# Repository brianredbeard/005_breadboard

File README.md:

# 005 Breadboard Breakout

## About

This is a breakout board for 0.05" (1.27mm) pitch parts so that they may be
connected to a standard 0.1" (2.54mm) pitch breadboard.

It was originally designed for use with the [Olimex iCE40HX8K-EVB][olimex-fpga].
This board uses a series of 40 pin IDC cables with 0.05" pitch which is great
from the perspective of maximizing the footprint of the development board...
it's sub-optimal for any peripheral development.  Additionally, this board
should be usable for other projects with similar footprint needs.

## Files

```
├── 005_breadboard-cache.lib          - a local copy of symbols used in the schematic
├── 005_breadboard.kicad_pcb          - kicad pcb layout file
├── 005_breadboard.pro                - project file (parameters for project)
├── 005_breadboard.sch                - kicad schematic file
├── 005_breadboard_schematic.pdf      - rendering of schematic in PDF
├── 005_breadboard_top.png            - 3d screenshot of board top
├── 005_breadboard_bottom.png         - 3d screenshot of board bottom
├── gerbers                           - gerber files for manufacturing
│   ├── 005_breadboard-B.Cu.gbl
│   ├── 005_breadboard-B.Mask.gbs
│   ├── 005_breadboard-B.SilkS.gbo
│   ├── 005_breadboard.drl
│   ├── 005_breadboard-Edge.Cuts.gm1
│   ├── 005_breadboard-F.Cu.gtl
│   ├── 005_breadboard-F.Mask.gts
│   └── 005_breadboard-F.SilkS.gto
└── .pretty                           - folder of local project footprints
```

## Screenshots

Top of board:

Bottom of board:

## Schematic

A simple PDF of the schematic can be downloaded [here](/005_breadboard_schematic.pdf)

## Bill of Materials

To build this board you will need the following:

| Part # | Quantity | Description |
| --     | --       | --          |
| 2x20 Pin Header | 1 | 2x20 0.05" (1.27mm) Pin header (male or female depending on need) |
| 1x20 Pin header (male) | 2  | 2x20 0.1" (2.54mm) Pin header (male) to be connected to breadboard |

The 0.05" pin headers can be sourced from a number of locations:

  - Olimex  - [female][olimex-ph5-f] / [male][olimex-ph5-m] 
  - Digikey - [female][digikey-ph5-f] / [male][digikey-ph5-m] 

The 0.10" pin headers can be sourced from a number of locations:

  - Digikey - [female][digikey-ph10-f] / [male][digikey-ph10-m] 

## Ordering

The board is currently shared on [OSHPark][oshpark] and can be ordered.  The
cost is $9.95 (USD) with a turnaround time of approximately 15 calendar days.

The Olimex [iCE40HX8K][olimex-fpga-source] evaluation board can be purchased
through [Olimex][olimex-fpga].

## LICENSE

These designs are licensed under the APACHE 2 license [LICENSE](LICENSE).

This design uses the [Olimex][olimex]  2x20 0.05" pitch SMD connectors from
their [KiCAD parts library][olimex-parts], which are also licensed under
APACHE 2.

[olimex]: https://www.olimex.com/
[olimex-fpga]: https://www.olimex.com/Products/FPGA/iCE40/iCE40HX8K-EVB/open-source-hardware
[olimex-fpga-source]: https://github.com/OLIMEX/iCE40HX8K-EVB
[olimex-parts]: https://github.com/OLIMEX/KiCAD
[oshpark]: https://oshpark.com/shared_projects/dG68p194

[olimex-ph5-f]: https://www.olimex.com/Products/Components/Connectors/FEMALE-YAV36P-2x05/
[olimex-ph5-m]: https://www.olimex.com/Products/Components/Connectors/MALE-PAV16X-2x05/

[digikey-ph5-f]: https://www.digikey.com/product-detail/en/amphenol-fci/20021321-00040T4LF/609-3779-ND/2209124
[digikey-ph5-m]: https://www.digikey.com/product-detail/en/harwin-inc/M50-3602042/952-1393-ND/2264374
[digikey-ph10-f]: https://www.digikey.com/product-detail/en/sullins-connector-solutions/PPPC201LFBN-RC/S7053-ND/810192
[digikey-ph10-m]: https://www.digikey.com/product-detail/en/sullins-connector-solutions/PRPC020SAAN-RC/S1011EC-20-ND/2775234

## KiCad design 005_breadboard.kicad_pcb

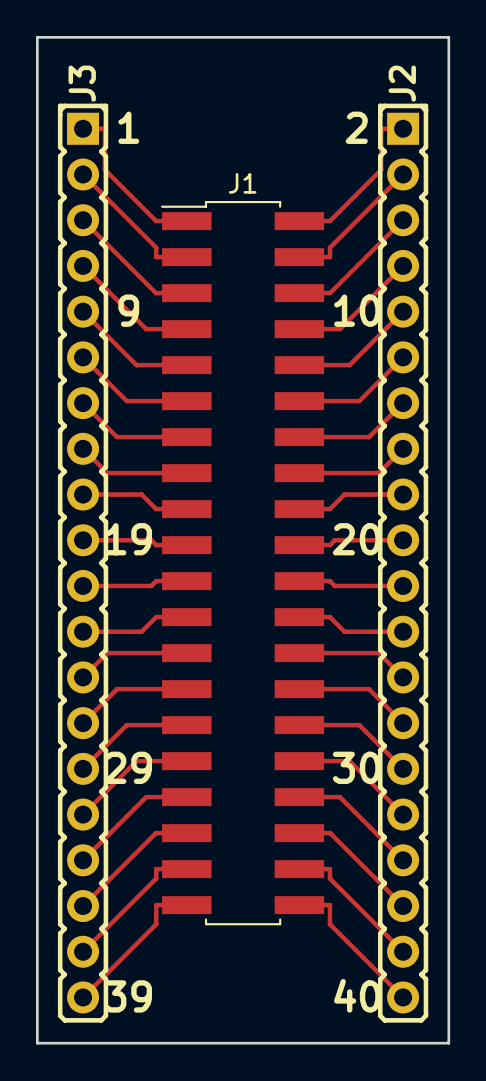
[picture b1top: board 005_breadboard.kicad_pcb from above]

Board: 2 copper layers, 22.9 x 55.9 mm, 3 parts (0 on the bottom side), 40 nets.

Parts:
J1: GPIO 02x20; Pin_Header_Straight_2x20_Pitch2.00mm_SMD
J2, J3: CONN_01X20; HN1x20

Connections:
/A1: J1.1, J3.1
/A2: J1.3, J3.2
/A3: J1.5, J3.3
/A4: J1.7, J3.4
/A5: J1.9, J3.5
/A6: J1.11, J3.6
/A7: J1.13, J3.7
/A8: J1.15, J3.8
/A9: J1.17, J3.9
/A10: J1.19, J3.10
/A11: J1.21, J3.11
/A12: J1.23, J3.12
/A13: J1.25, J3.13
/A14: J1.27, J3.14
/A15: J1.29, J3.15
/A16: J1.31, J3.16
/A17: J1.33, J3.17
/A18: J1.35, J3.18
/A19: J1.37, J3.19
/A20: J1.39, J3.20
/A21: J1.2, J2.1
/A22: J1.4, J2.2
/A23: J1.6, J2.3
/A24: J1.8, J2.4
/A25: J1.10, J2.5
/A26: J1.12, J2.6
/A27: J1.14, J2.7
/A28: J1.16, J2.8
/A29: J1.18, J2.9
/A30: J1.20, J2.10
/A31: J1.22, J2.11
/A32: J1.24, J2.12
/A33: J1.26, J2.13
/A34: J1.28, J2.14
/A35: J1.30, J2.15
/A36: J1.32, J2.16
/A37: J1.34, J2.17
/A38: J1.36, J2.18
/A39: J1.38, J2.19
/A40: J1.40, J2.20

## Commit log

2017-09-20 Open Sourcing the board designs
    The initial order has now been placed with OSHPark so I'll follow up in
    a few weeks with any design tweaks.
2017-09-20 Reference links for new users
    Adding explicit links to both rendered images of the board as well as a
    PDF of the schematic.
2017-09-20 doc: Bill of Materials
    Adding a list of components and links from where they may be sourced.
2017-09-20 doc: Updating link iCE40 board sources
    Fixed the link to the Lattice board's KiCAD sources. Previously the
    hyperlink was pointing to the Olimex KiCAD libraries.
